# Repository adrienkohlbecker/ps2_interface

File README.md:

# PS/2 interface

## Board

## Schematic

## BOM

| Refs | Qty | Component | Description |
| ----- | --- | ---- | ----------- |
| C1 | 1 | 10nF | Unpolarized capacitor D4.3mm_W1.9mm_P5.00mm |
| C2, C3, C4, C5, C6, C7 | 6 | 0.1uF | Unpolarized capacitor D3.0mm_W1.6mm_P2.50mm |
| C8 | 1 | 10uF | Polarized capacitor D4.0mm_P2.00mm |
| D1, D2, D3 | 3 | 1N5817 | 20V 1A Schottky Barrier Rectifier Diode, DO-41 |
| J1 | 1 | Mini-DIN-6 | 6-pin Mini-DIN connector, EB-DIOS M06V |
| J2 | 1 | Conn_01x14 | Generic connector, single row, 01x14 |
| J3 | 1 | KBD | Generic connector, single row, 01x02 |
| R1 | 1 | 22k | Resistor DIN0207 |
| R2, R3, R4 | 3 | 10k | Resistor DIN0207 |
| TP3 | 1 | GND | test point D2.60mm_Drill1.6mm |
| U1, U2 | 2 | 74HC595 | 8-bit serial in/out Shift Register 3-State Outputs, DIP-16 |
| U3 | 1 | 74HC74 | Dual D Flip-flop, Set & Reset, DIP-14 |
| U4 | 1 | 74HC08 | Quad And2, DIP-14 |
| U5 | 1 | 74HC14 | Hex inverter schmitt trigger, DIP-14 |
| U6 | 1 | 74HC280 | Parity Generator/Checker, DIP-14 |

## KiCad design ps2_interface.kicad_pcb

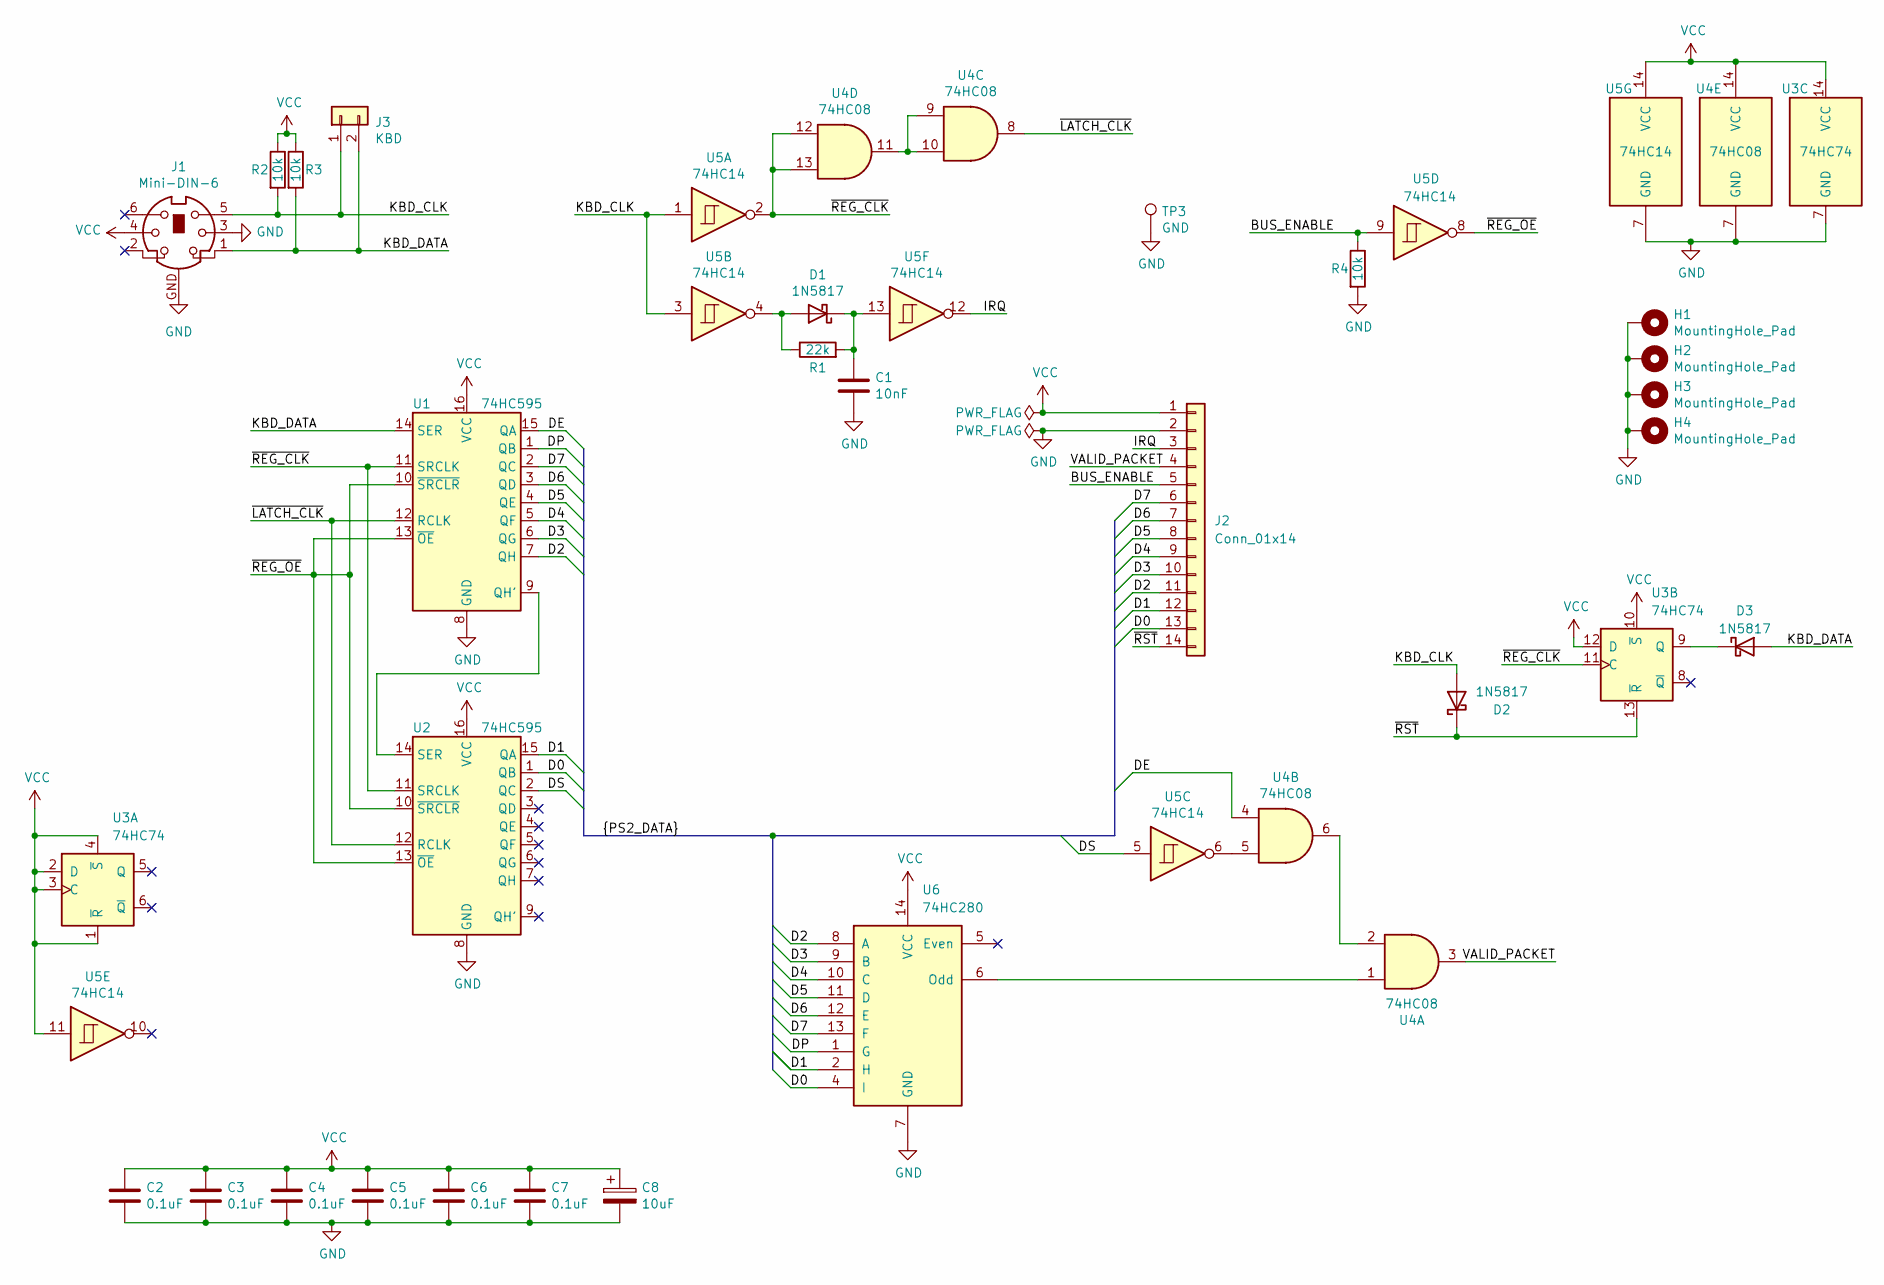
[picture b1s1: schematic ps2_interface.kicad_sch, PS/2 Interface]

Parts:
C1: 10nF; C_Disc_D4.3mm_W1.9mm_P5.00mm
C2, C3, C4, C5, C6, C7: 0.1uF; C_Disc_D3.0mm_W1.6mm_P2.50mm
C8: 10uF; CP_Radial_D4.0mm_P2.00mm
D1, D2, D3: 1N5817; D_DO-41_SOD81_P7.62mm_Horizontal
H1, H2, H3, H4: MountingHole_Pad; MountingHole_3.2mm_M3_Pad
J1: Mini-DIN-6; PS2_mini_din_6
J2: Conn_01x14; PinHeader_1x14_P2.54mm_Vertical
J3: KBD; PinSocket_1x02_P2.54mm_Vertical
R1: 22k; R_Axial_DIN0207_L6.3mm_D2.5mm_P7.62mm_Horizontal
R2, R3, R4: 10k; R_Axial_DIN0207_L6.3mm_D2.5mm_P7.62mm_Horizontal
TP3: GND; TestPoint_Loop_D2.60mm_Drill1.6mm_Beaded
U1, U2: 74HC595; DIP-16_W7.62mm
U3: 74HC74; DIP-14_W7.62mm
U4: 74HC08; DIP-14_W7.62mm
U5: 74HC14; DIP-14_W7.62mm
U6: 74HC280; DIP-14_W7.62mm

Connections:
/BUS_ENABLE: J2.5, R4.1, U5.9
/D0: J2.13, U2.1 (QB), U6.4 (I)
/D1: J2.12, U2.15 (QA), U6.2 (H)
/D2: J2.11, U1.7 (QH), U6.8 (A)
/D3: J2.10, U1.6 (QG), U6.9 (B)
/D4: J2.9, U1.5 (QF), U6.10 (C)
/D5: J2.8, U1.4 (QE), U6.11 (D)
/D6: J2.7, U1.3 (QD), U6.12 (E)
/D7: J2.6, U1.2 (QC), U6.13 (F)
/DE: U1.15 (QA), U4.4
/DP: U1.1 (QB), U6.1 (G)
/DS: U2.2 (QC), U5.5
/IRQ: J2.3, U5.12
/KBD_CLK: D2.2 (A), J1.5, J3.1, R2.2, U5.1, U5.3
/KBD_DATA: D3.2 (A), J1.1, J3.2, R3.2, U1.14 (SER)
/VALID_PACKET: J2.4, U4.3
/~LATCH_CLK: U1.12 (RCLK), U2.12 (RCLK), U4.8
/~REG_CLK: U1.11 (SRCLK), U2.11 (SRCLK), U3.11 (C), U4.12, U4.13, U5.2
/~REG_OE: U1.10 (~SRCLR), U1.13 (~OE), U2.10 (~SRCLR), U2.13 (~OE), U5.8
/~RST: D2.1 (K), J2.14, U3.13 (~R)
GND: C1.2, C2.2, C3.2, C4.2, C5.2, C6.2, C7.2, C8.2, H1.1, H2.1, H3.1, H4.1, J1.3, J1.GND, J2.2, R4.2, TP3.1, U1.8 (GND), U2.8 (GND), U3.7 (GND), U4.7 (GND), U5.7 (GND), U6.7 (GND)
unnamed: D1.2 (A), R1.1, U5.4
unnamed: C1.1, D1.1 (K), R1.2, U5.13
unnamed: D3.1 (K), U3.9 (Q)
unnamed: U1.9 (QH'), U2.14 (SER)
unnamed: U4.2, U4.6
unnamed: U4.5, U5.6
unnamed: U4.9, U4.10, U4.11
unnamed: U4.1, U6.6 (Odd)
VCC: C2.1, C3.1, C4.1, C5.1, C6.1, C7.1, C8.1, J1.4, J2.1, R2.1, R3.1, U1.16 (VCC), U2.16 (VCC), U3.1 (~R), U3.2 (D), U3.3 (C), U3.4 (~S), U3.10 (~S), U3.12 (D), U3.14 (VCC), U4.14 (VCC), U5.11, U5.14 (VCC), U6.14 (VCC)

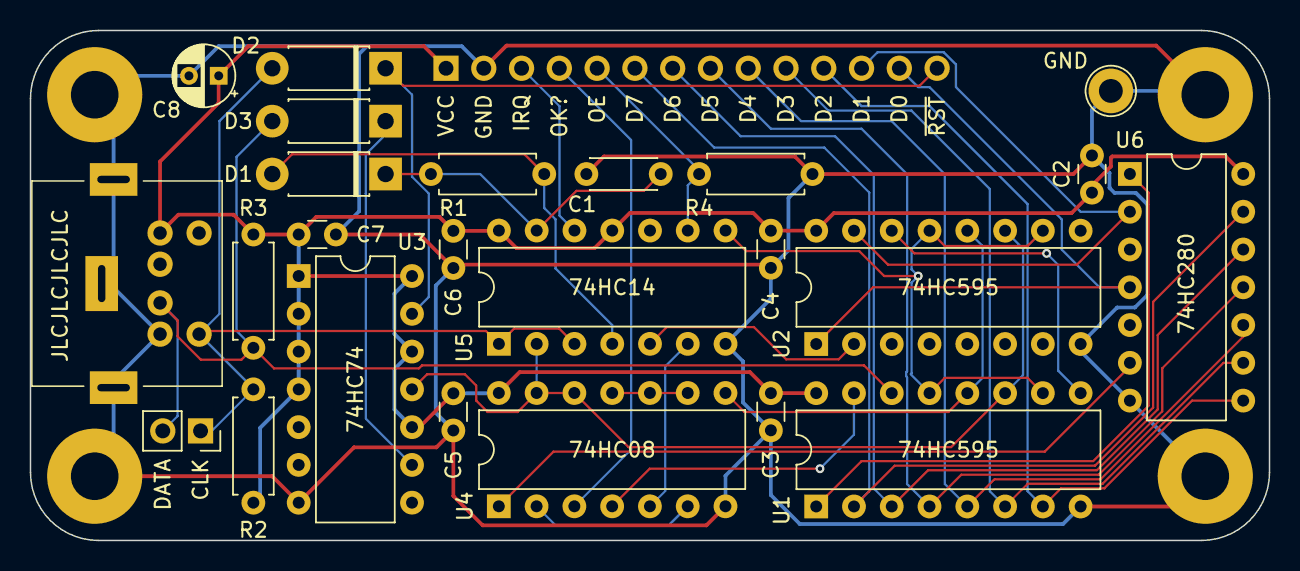
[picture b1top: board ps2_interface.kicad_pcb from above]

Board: 2 copper layers, 83.3 x 34.3 mm, 29 parts (1 on the bottom side), 30 nets.

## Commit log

2021-05-18 Add keyboard project
2021-05-30 Update keyboard
2021-07-13 Update keyboard PCB
2021-08-04 Updated keyboard
2021-12-19 Remove ignored files
2023-06-07 Update for KiCad 6
2023-06-23 Add auto reset

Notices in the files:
ps2_interface.kicad_pcb:
Licensed under CERN-OHL-W v2
Copyright © Adrien Kohlbecker
